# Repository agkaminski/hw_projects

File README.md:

# hw_projects

Various hardware projects that do not deserve their own repository.

## Contents

- [DIYosc](DIYosc) - make your own custom DIP oscilator using HC49 SMD crystal,
- [flipperzero_esp](flipperzero_esp) - expansion module with ESP32 for Flipper Zero,
- [LEDclock](ledclock) - big DIY clock based on LED filaments,
- [picocalc-pi-zero-2](picocalc-pi-zero-2) - Adapter to replace Raspberry Pico with Raspberry Pi Zero in Clockwork PicoCalc.
- [rs232usb](rs232usb) - RS232 to USB-C adapter designed to be pluged directly into the host device,
- [skadis_clock](skadis_clock) - LED clock that fits behind the IKEA SKÅDIS pegboard,
- [usbasp](usbasp) - my realization of the famous [usbasp](https://www.fischl.de/usbasp/),
- [usbasp_mini](usbasp_mini) - miniature version of mine usbasp **design not proven**,
- [VGAtest](VGAtest) - proof of concept 80x40 B&W text mode VGA adapter.

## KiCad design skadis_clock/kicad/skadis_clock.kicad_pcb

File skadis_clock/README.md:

# skadis-clock

LED digital clock that fits behind the IKEA SKÅDIS pegboard.
Uses deformed 7-segment display that shines through pegboard slots.

# PCB

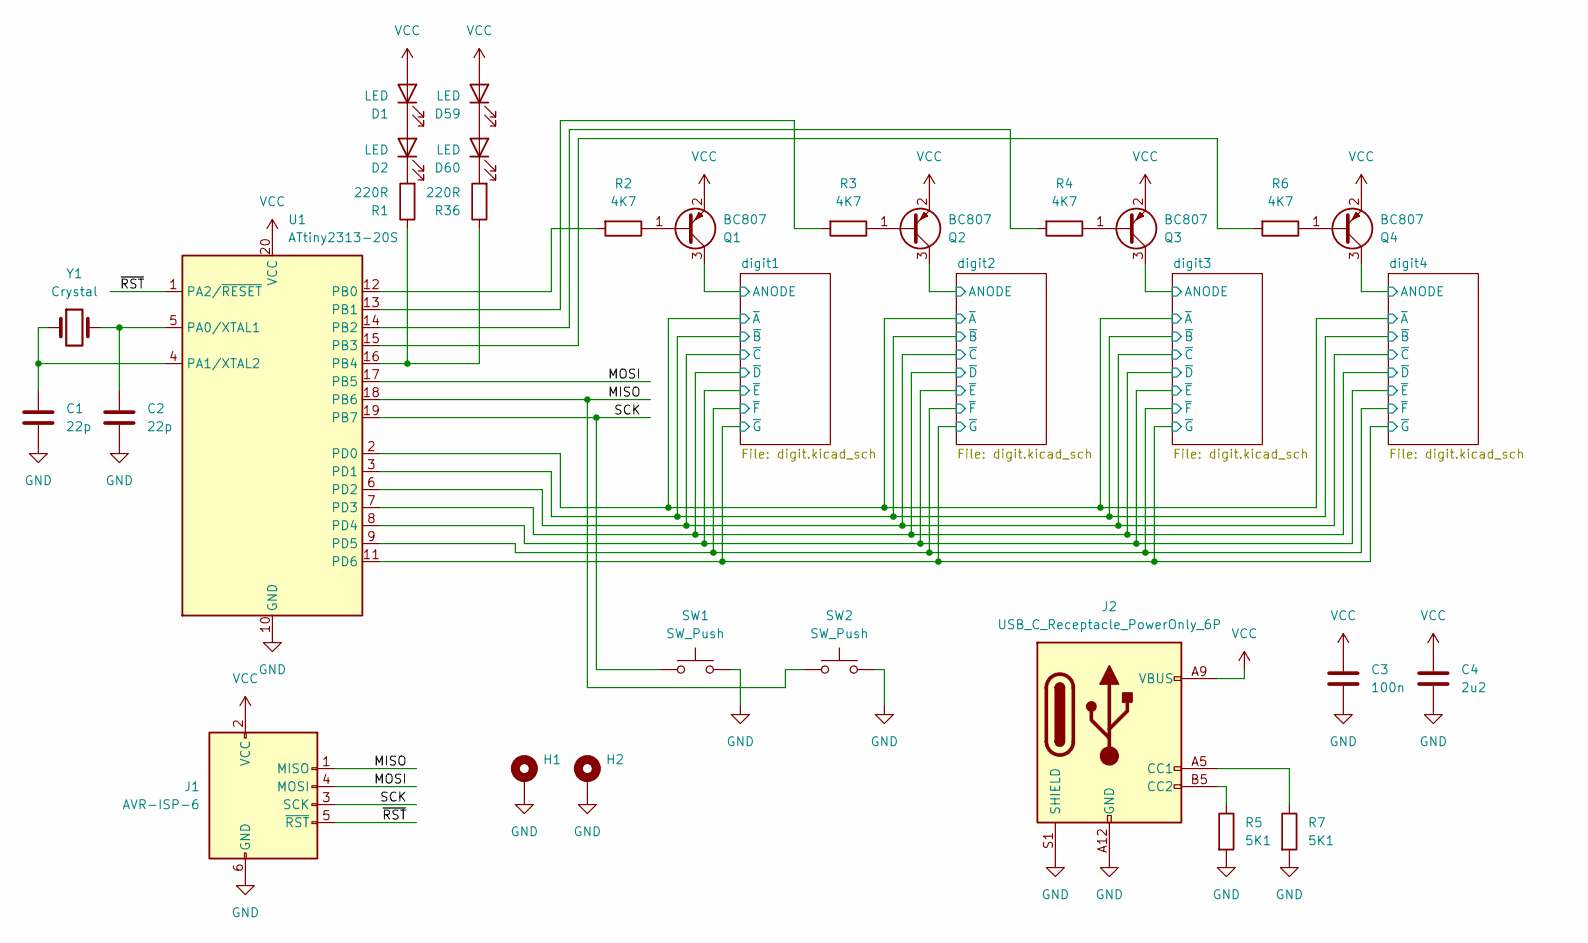
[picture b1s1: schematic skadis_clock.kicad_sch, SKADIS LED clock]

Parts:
C1, C2: 22p; C_0805_2012Metric
C3: 100n; C_0805_2012Metric
C4: 2u2; C_0805_2012Metric
D1, D2, D59, D60: LED; LED_D5.0mm
H1, H2: MountingHole_3.2mm_M3_Pad_Via
J1: AVR-ISP-6; IDC-Header_2x03_P2.54mm_Vertical
J2: USB_C_Receptacle_PowerOnly_6P; USB_C_Receptacle_GCT_USB4125-xx-x-0190_6P_TopMnt_Horizontal
Q1, Q2, Q3, Q4: BC807; SOT-23
R1, R36: 220R; R_0805_2012Metric
R2, R3, R4, R6: 4K7; R_0805_2012Metric
R5, R7: 5K1; R_0805_2012Metric
SW1, SW2: SW_Push; SW_Tactile_SPST_NO_Straight_CK_PTS636Sx25SMTRLFS
U1: ATtiny2313-20S; SOIC-20W_7.5x12.8mm_P1.27mm
Y1: Crystal; Crystal_SMD_HC49-SD

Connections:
/MISO: J1.1 (MISO), SW2.1, U1.18 (PB6)
/MOSI: J1.4 (MOSI), U1.17 (PB5)
/SCK: J1.3 (SCK), SW1.1, U1.19 (PB7)
/digit1/ANODE: Q1.3 (C); also elsewhere on the board
/digit1/~A: U1.2 (PD0); also elsewhere on the board
/digit1/~B: U1.3 (PD1); also elsewhere on the board
/digit1/~C: U1.6 (PD2); also elsewhere on the board
/digit1/~D: U1.7 (PD3); also elsewhere on the board
/digit1/~E: U1.8 (PD4); also elsewhere on the board
/digit1/~F: U1.9 (PD5); also elsewhere on the board
/digit1/~G: U1.11 (PD6); also elsewhere on the board
/digit2/ANODE: Q2.3 (C); also elsewhere on the board
/digit3/ANODE: Q3.3 (C); also elsewhere on the board
/digit4/ANODE: Q4.3 (C); also elsewhere on the board
/~RST: J1.5 (~RST), U1.1 (PA2/~RESET)
GND: C1.2, C2.2, C3.2, C4.2, H1.MP, H2.MP, J1.6 (GND), J2.A12 (GND), J2.B12 (GND), J2.S1 (SHIELD), R5.2, R7.2, SW1.2, SW2.2, U1.10 (GND)
unnamed: D1.1 (K), D2.2 (A)
unnamed: D2.1 (K), R1.2
unnamed: D59.1 (K), D60.2 (A)
unnamed: D60.1 (K), R36.2
unnamed: J2.A5 (CC1), R7.1
unnamed: J2.B5 (CC2), R5.1
unnamed: Q1.1 (B), R2.1
unnamed: Q2.1 (B), R3.1
unnamed: Q3.1 (B), R4.1
unnamed: Q4.1 (B), R6.1
unnamed: C2.1, U1.5 (PA0/XTAL1), Y1.2
unnamed: C1.1, U1.4 (PA1/XTAL2), Y1.1
unnamed: R2.2, U1.12 (PB0)
unnamed: R3.2, U1.13 (PB1)
unnamed: R4.2, U1.14 (PB2)
unnamed: R6.2, U1.15 (PB3)
unnamed: R1.1, R36.1, U1.16 (PB4)
VCC: C3.1, C4.1, D1.2 (A), D59.2 (A), J1.2 (VCC), J2.A9 (VBUS), J2.B9 (VBUS), Q1.2 (E), Q2.2 (E), Q3.2 (E), Q4.2 (E), U1.20 (VCC)

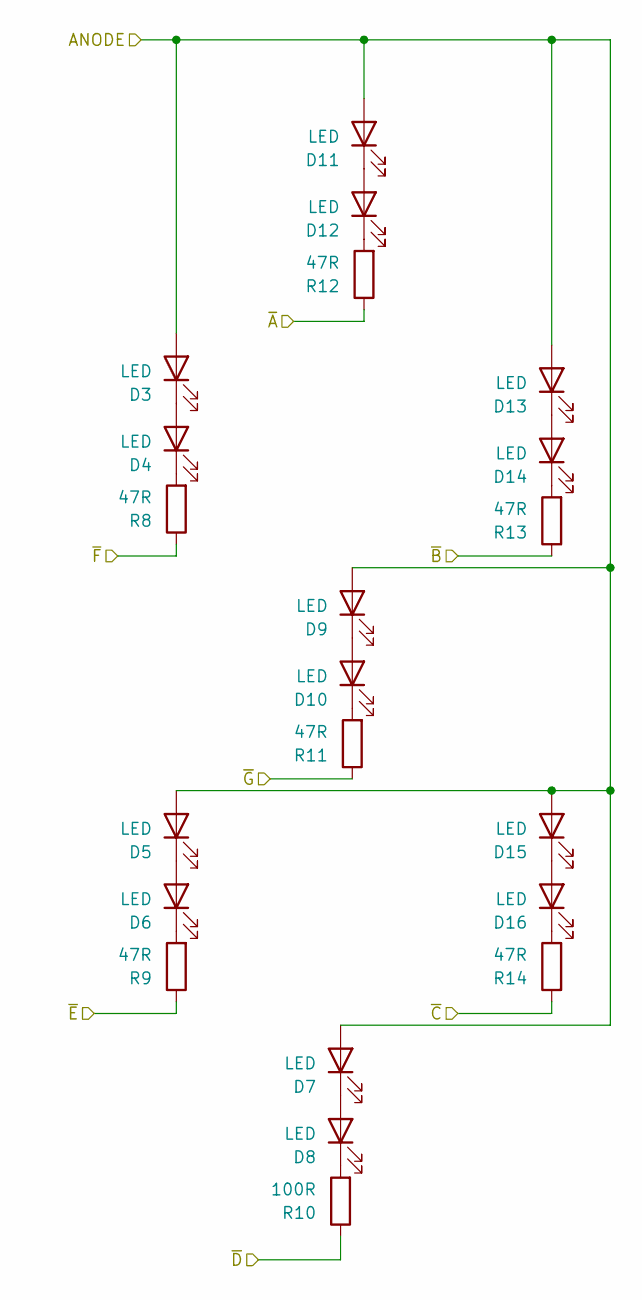
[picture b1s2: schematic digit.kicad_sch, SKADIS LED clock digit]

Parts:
D3, D4, D5, D6, D7, D8, D9, D10, D11, D12, D13, D14, D15, D16: LED; LED_D5.0mm
R8, R9, R11, R12, R13, R14: 47R; R_0805_2012Metric
R10: 100R; R_0805_2012Metric

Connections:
/digit1/ANODE: D3.2 (A), D5.2 (A), D7.2 (A), D9.2 (A), D11.2 (A), D13.2 (A), D15.2 (A); also elsewhere on the board
/digit1/~A: R12.1; also elsewhere on the board
/digit1/~B: R13.1; also elsewhere on the board
/digit1/~C: R14.1; also elsewhere on the board
/digit1/~D: R10.1; also elsewhere on the board
/digit1/~E: R9.1; also elsewhere on the board
/digit1/~F: R8.1; also elsewhere on the board
/digit1/~G: R11.1; also elsewhere on the board
unnamed: D3.1 (K), D4.2 (A)
unnamed: D4.1 (K), R8.2
unnamed: D5.1 (K), D6.2 (A)
unnamed: D6.1 (K), R9.2
unnamed: D7.1 (K), D8.2 (A)
unnamed: D8.1 (K), R10.2
unnamed: D9.1 (K), D10.2 (A)
unnamed: D10.1 (K), R11.2
unnamed: D11.1 (K), D12.2 (A)
unnamed: D12.1 (K), R12.2
unnamed: D13.1 (K), D14.2 (A)
unnamed: D14.1 (K), R13.2
unnamed: D15.1 (K), D16.2 (A)
unnamed: D16.1 (K), R14.2

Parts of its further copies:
D17, D18, D19, D20, D21, D22, D23, D24, D25, D26, D27, D28, D29, D30, D31, D32, D33, D34, D35, D36, D37, D38, D39, D40, D41, D42, D43, D44, D45, D46, D47, D48, D49, D50, D51, D52, D53, D54, D55, D56, D57, D58: LED; LED_D5.0mm
R15, R16, R18, R19, R20, R21, R22, R23, R25, R26, R27, R28, R29, R30, R32, R33, R34, R35: 47R; R_0805_2012Metric
R17, R24, R31: 100R; R_0805_2012Metric

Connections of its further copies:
/digit1/~A: R19.1, R26.1, R33.1; also elsewhere on the board
/digit1/~B: R20.1, R27.1, R34.1; also elsewhere on the board
/digit1/~C: R21.1, R28.1, R35.1; also elsewhere on the board
/digit1/~D: R17.1, R24.1, R31.1; also elsewhere on the board
/digit1/~E: R16.1, R23.1, R30.1; also elsewhere on the board
/digit1/~F: R15.1, R22.1, R29.1; also elsewhere on the board
/digit1/~G: R18.1, R25.1, R32.1; also elsewhere on the board
/digit2/ANODE: D17.2 (A), D19.2 (A), D21.2 (A), D23.2 (A), D25.2 (A), D27.2 (A), D29.2 (A); also elsewhere on the board
/digit3/ANODE: D31.2 (A), D33.2 (A), D35.2 (A), D37.2 (A), D39.2 (A), D41.2 (A), D43.2 (A); also elsewhere on the board
/digit4/ANODE: D45.2 (A), D47.2 (A), D49.2 (A), D51.2 (A), D53.2 (A), D55.2 (A), D57.2 (A); also elsewhere on the board
unnamed: D17.1 (K), D18.2 (A)
unnamed: D18.1 (K), R15.2
unnamed: D19.1 (K), D20.2 (A)
unnamed: D20.1 (K), R16.2
unnamed: D21.1 (K), D22.2 (A)
unnamed: D22.1 (K), R17.2
unnamed: D23.1 (K), D24.2 (A)
unnamed: D24.1 (K), R18.2
unnamed: D25.1 (K), D26.2 (A)
unnamed: D26.1 (K), R19.2
unnamed: D27.1 (K), D28.2 (A)
unnamed: D28.1 (K), R20.2
unnamed: D29.1 (K), D30.2 (A)
unnamed: D30.1 (K), R21.2
unnamed: D31.1 (K), D32.2 (A)
unnamed: D32.1 (K), R22.2
unnamed: D33.1 (K), D34.2 (A)
unnamed: D34.1 (K), R23.2
unnamed: D35.1 (K), D36.2 (A)
unnamed: D36.1 (K), R24.2
unnamed: D37.1 (K), D38.2 (A)
unnamed: D38.1 (K), R25.2
unnamed: D39.1 (K), D40.2 (A)
unnamed: D40.1 (K), R26.2
unnamed: D41.1 (K), D42.2 (A)
unnamed: D42.1 (K), R27.2
unnamed: D43.1 (K), D44.2 (A)
unnamed: D44.1 (K), R28.2
unnamed: D45.1 (K), D46.2 (A)
unnamed: D46.1 (K), R29.2
unnamed: D47.1 (K), D48.2 (A)
unnamed: D48.1 (K), R30.2
unnamed: D49.1 (K), D50.2 (A)
unnamed: D50.1 (K), R31.2
unnamed: D51.1 (K), D52.2 (A)
unnamed: D52.1 (K), R32.2
unnamed: D53.1 (K), D54.2 (A)
unnamed: D54.1 (K), R33.2
unnamed: D55.1 (K), D56.2 (A)
unnamed: D56.1 (K), R34.2
unnamed: D57.1 (K), D58.2 (A)
unnamed: D58.1 (K), R35.2

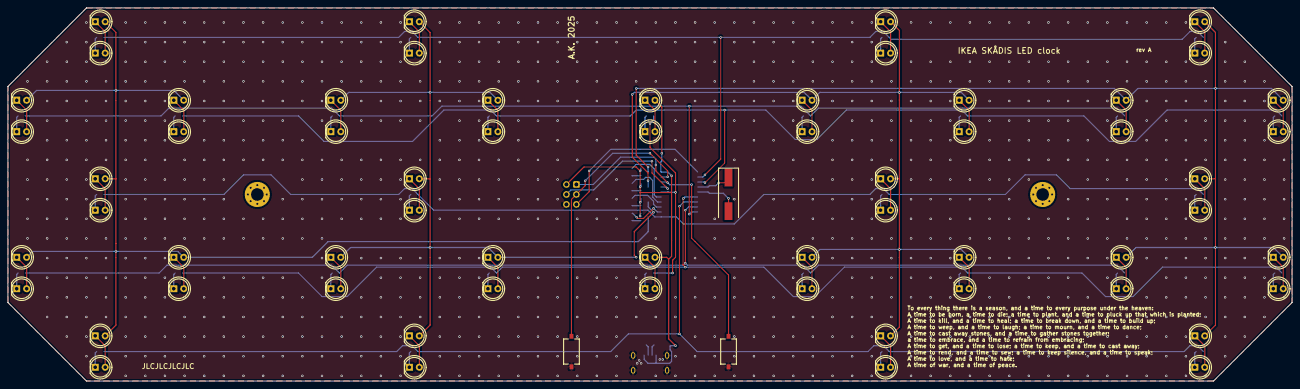
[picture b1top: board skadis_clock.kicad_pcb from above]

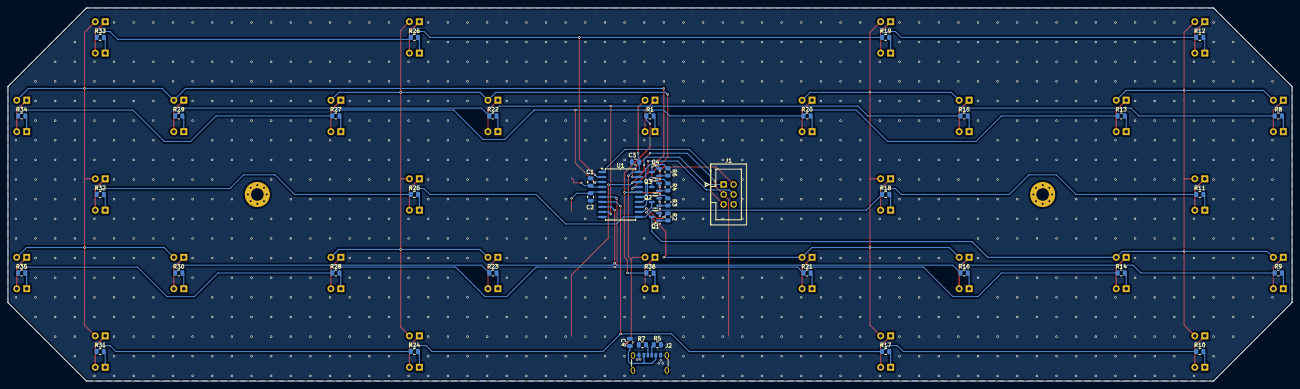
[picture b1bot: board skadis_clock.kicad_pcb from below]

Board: 2 copper layers, 327.0 x 95.0 mm, 112 parts (47 on the bottom side), 90 nets.

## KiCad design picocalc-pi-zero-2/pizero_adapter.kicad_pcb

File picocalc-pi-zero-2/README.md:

# picocalc-pi-zero-2

Adapter to replace Raspberry Pico with Raspberry Pi Zero in Clockwork PicoCalc.

According to [https://github.com/wasdwasd0105/picocalc-pi-zero-2](https://github.com/wasdwasd0105/picocalc-pi-zero-2).

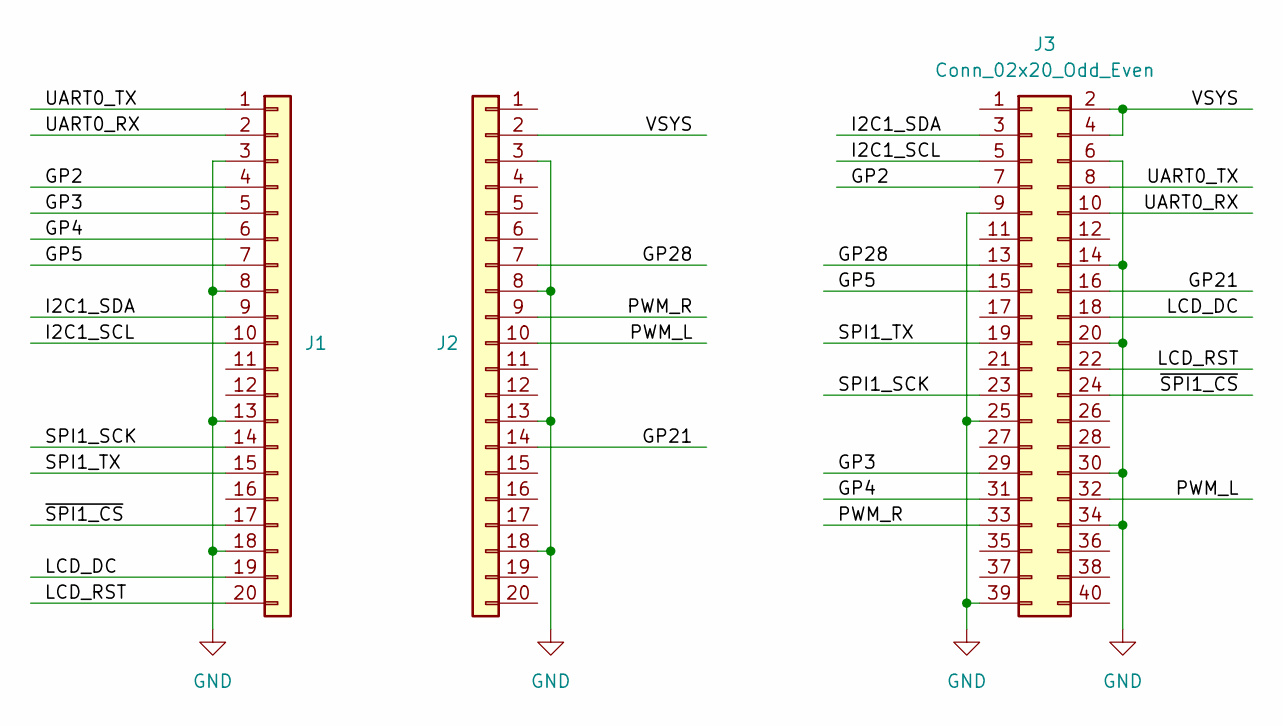
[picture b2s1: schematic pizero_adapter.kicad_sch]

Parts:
J1, J2: Conn_01x20; PinHeader_1x20_P2.54mm_Vertical
J3: Conn_02x20_Odd_Even; PinHeader_2x20_P2.54mm_Vertical

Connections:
/GP2: J1.4, J3.7
/GP3: J1.5, J3.29
/GP4: J1.6, J3.31
/GP5: J1.7, J3.15
/GP21: J2.14, J3.16
/GP28: J2.7, J3.13
/I2C1_SCL: J1.10, J3.5
/I2C1_SDA: J1.9, J3.3
/LCD_DC: J1.19, J3.18
/LCD_RST: J1.20, J3.22
/PWM_L: J2.10, J3.32
/PWM_R: J2.9, J3.33
/SPI1_SCK: J1.14, J3.23
/SPI1_TX: J1.15, J3.19
/UART0_RX: J1.2, J3.10
/UART0_TX: J1.1, J3.8
/VSYS: J2.2, J3.2, J3.4
/~SPI1_CS: J1.17, J3.24
GND: J1.3, J1.8, J1.13, J1.18, J2.3, J2.8, J2.13, J2.18, J3.6, J3.9, J3.14, J3.20, J3.25, J3.30, J3.34, J3.39

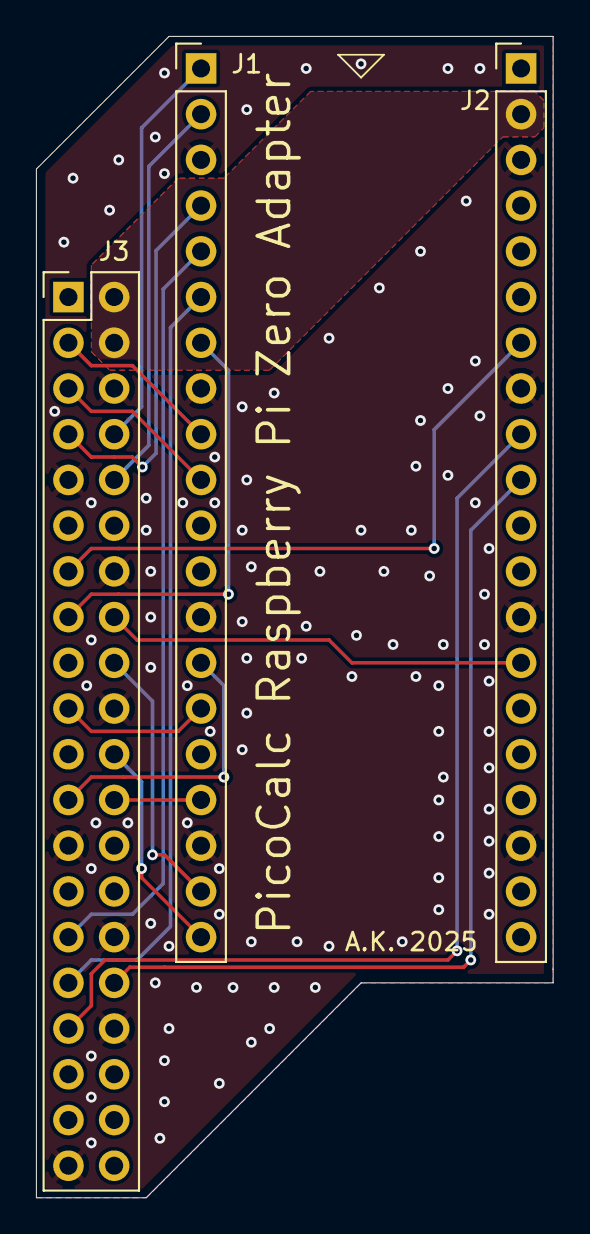
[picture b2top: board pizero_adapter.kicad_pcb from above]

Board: 2 copper layers, 28.7 x 64.5 mm, 3 parts (0 on the bottom side), 19 nets.

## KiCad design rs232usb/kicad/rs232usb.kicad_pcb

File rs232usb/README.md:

# rs232usb

RS232 to USB-C adapter based on CH340N and MAX232.
Designed to be pluged directly into the host device (i.e into male plug).

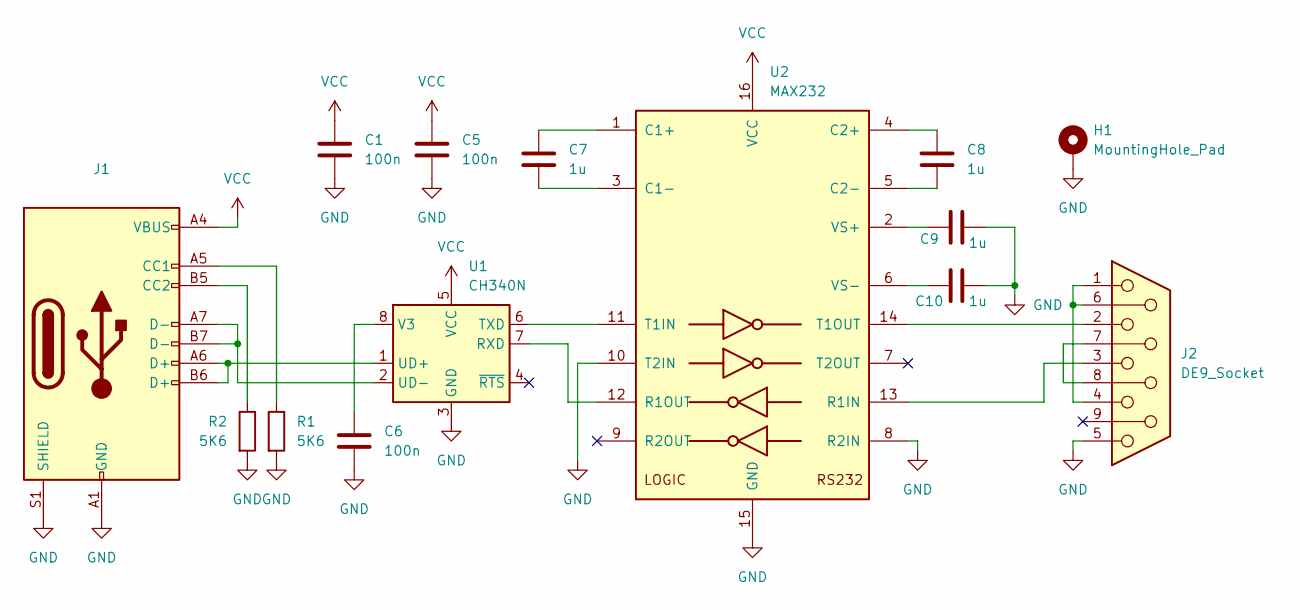
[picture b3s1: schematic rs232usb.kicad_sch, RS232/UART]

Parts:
C1, C5, C6: 100n; C_0805_2012Metric
C7, C8, C9, C10: 1u; C_0805_2012Metric
H1: MountingHole_Pad; MountingHole_3.2mm_M3_Pad_Via
J1: USB_C_Receptacle_USB2.0_14P; USB_C_Receptacle_GCT_USB4105-xx-A_16P_TopMnt_Horizontal
J2: DE9_Socket; DSUB-9_Socket_EdgeMount_P2.77mm
R1, R2: 5K6; R_0805_2012Metric
U1: CH340N; SOP-8_3.9x4.9mm_P1.27mm
U2: MAX232; SOIC-16_3.9x9.9mm_P1.27mm

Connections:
GND: C1.2, C5.2, C6.2, C9.1, C10.1, H1.1, J1.A1 (GND), J1.A12 (GND), J1.B1 (GND), J1.B12 (GND), J1.S1 (SHIELD), J2.5, R1.2, R2.2, U1.3 (GND), U2.8 (R2IN), U2.10 (T2IN), U2.15 (GND)
unnamed: J1.A5 (CC1), R1.1
unnamed: J1.B5 (CC2), R2.1
unnamed: J2.1, J2.4, J2.6
unnamed: J2.7, J2.8
unnamed: U1.7 (RXD), U2.12 (R1OUT)
unnamed: U1.6 (TXD), U2.11 (T1IN)
unnamed: J1.A6 (D+), J1.B6 (D+), U1.1 (UD+)
unnamed: J1.A7 (D-), J1.B7 (D-), U1.2 (UD-)
unnamed: C6.1, U1.8 (V3)
unnamed: C7.1, U2.1 (C1+)
unnamed: C7.2, U2.3 (C1-)
unnamed: C8.2, U2.4 (C2+)
unnamed: C8.1, U2.5 (C2-)
unnamed: J2.3, U2.13 (R1IN)
unnamed: J2.2, U2.14 (T1OUT)
unnamed: C9.2, U2.2 (VS+)
unnamed: C10.2, U2.6 (VS-)
VCC: C1.1, C5.1, J1.A4 (VBUS), J1.A9 (VBUS), J1.B4 (VBUS), J1.B9 (VBUS), U1.5 (VCC), U2.16 (VCC)

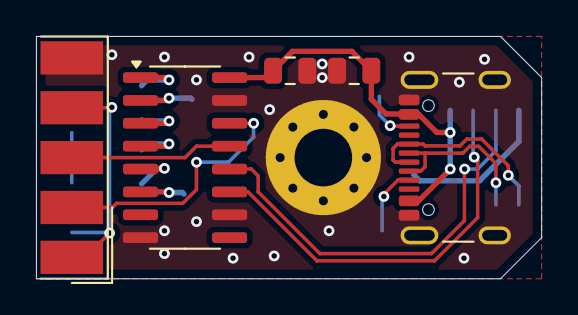
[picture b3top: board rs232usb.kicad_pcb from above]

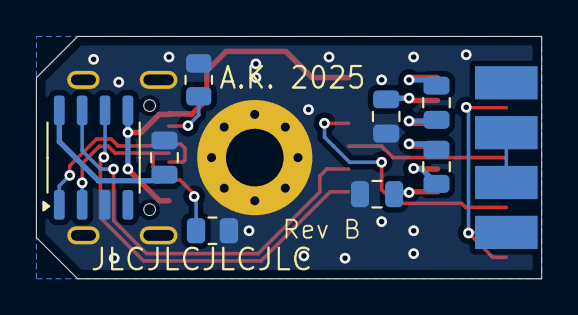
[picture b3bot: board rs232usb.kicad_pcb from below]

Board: 2 copper layers, 28.1 x 13.5 mm, 14 parts (8 on the bottom side), 19 nets.

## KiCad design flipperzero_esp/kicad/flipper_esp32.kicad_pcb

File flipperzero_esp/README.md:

# flipperzero_esp

Expansion module with ESP32 for Flipper Zero.

## Patch

Adapts [ESP flasher app](https://github.com/0xchocolate/flipperzero-esp-flasher) to the changes in pinout I made.

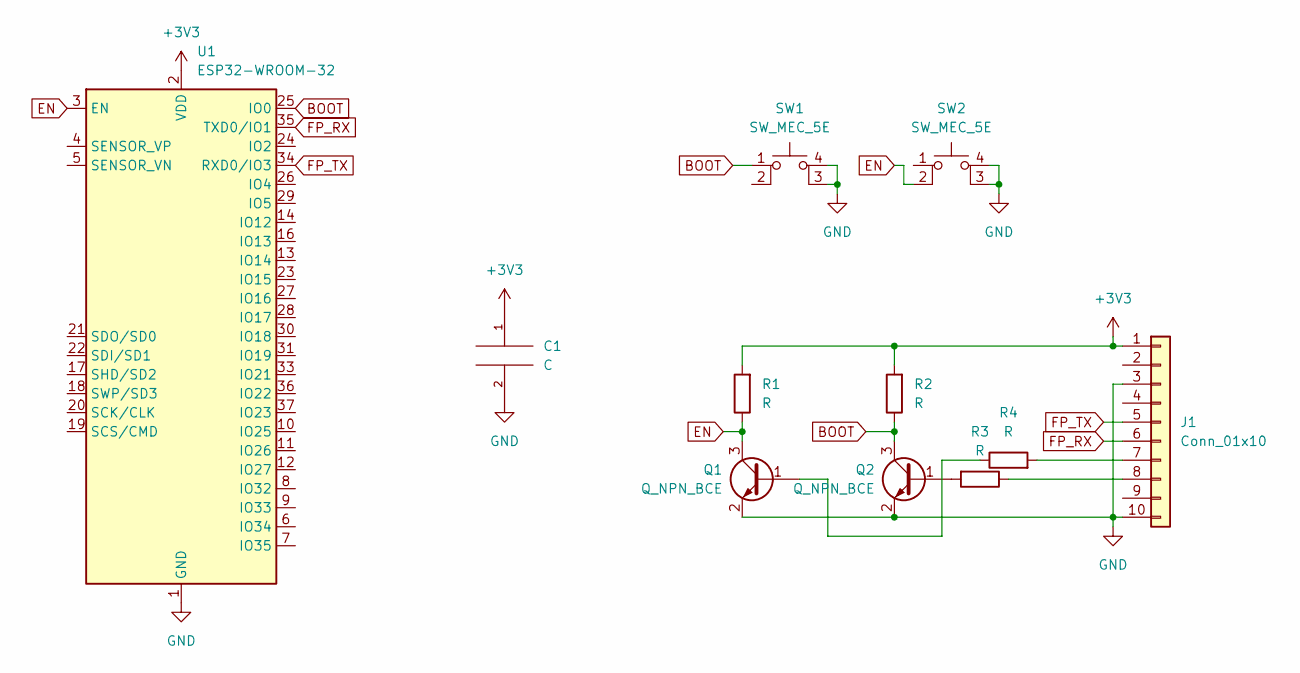
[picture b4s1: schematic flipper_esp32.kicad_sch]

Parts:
C1: C; C_0805_2012Metric_Pad1.18x1.45mm_HandSolder
J1: Conn_01x10; PinSocket_1x10_P2.54mm_Horizontal
Q1, Q2: Q_NPN_BCE; SOT-23W_Handsoldering
R1, R2, R3, R4: R; R_0805_2012Metric_Pad1.20x1.40mm_HandSolder
SW1, SW2: SW_MEC_5E; SW_SPST_Omron_B3FS-101xP
U1: ESP32-WROOM-32

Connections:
+3V3: C1.1, J1.1, R1.2, R2.2, U1.2 (VDD)
BOOT: Q2.3 (E), R2.1, SW1.1, U1.25 (IO0)
EN: Q1.3 (E), R1.1, SW2.2, U1.3 (EN)
FP_RX: J1.6, U1.35 (TXD0/IO1)
FP_TX: J1.5, U1.34 (RXD0/IO3)
GND: C1.2, J1.3, J1.10, Q1.2 (C), Q2.2 (C), SW1.3 (K), SW1.4 (A), SW2.3 (K), SW2.4 (A), U1.1 (GND), U1.15 (GND), U1.38 (GND), U1.39 (GND)
unnamed: J1.7, R4.2
unnamed: J1.8, R3.1
unnamed: Q1.1 (B), R4.1
unnamed: Q2.1 (B), R3.2

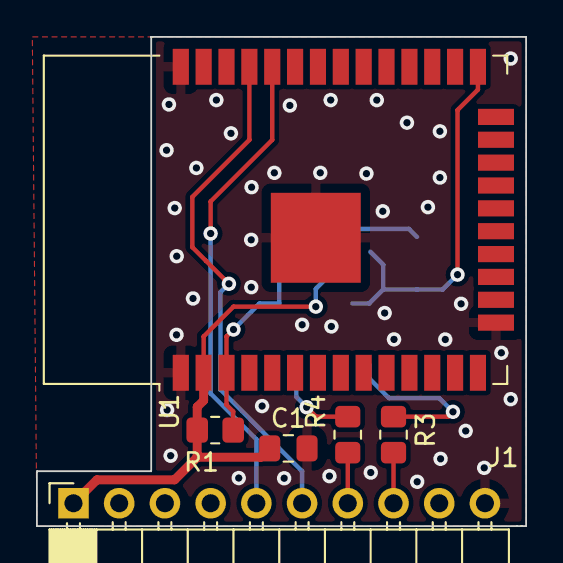
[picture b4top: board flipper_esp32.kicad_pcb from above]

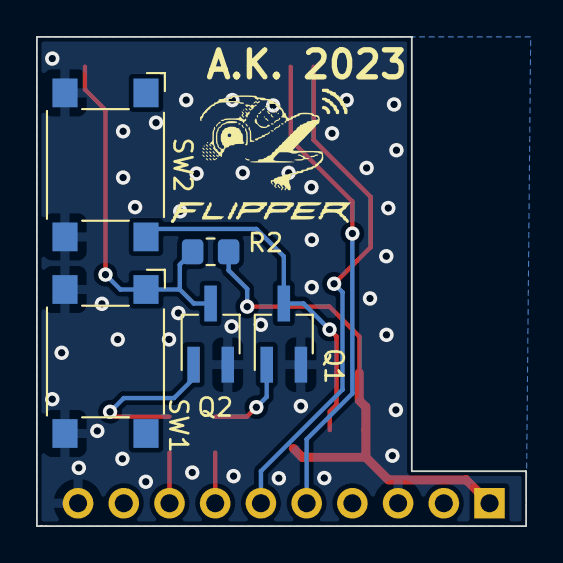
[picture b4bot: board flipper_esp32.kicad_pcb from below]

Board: 2 copper layers, 27.2 x 27.2 mm, 11 parts (5 on the bottom side), 10 nets.

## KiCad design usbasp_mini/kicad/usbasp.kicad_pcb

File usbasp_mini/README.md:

# usbasp_mini

My realization of the famous [usbasp](https://www.fischl.de/usbasp/).
Enhanced with logic level shifters to allow wide range of targed Vdd's.

Miniature version, equiped with the 6 pin ISP connector only.

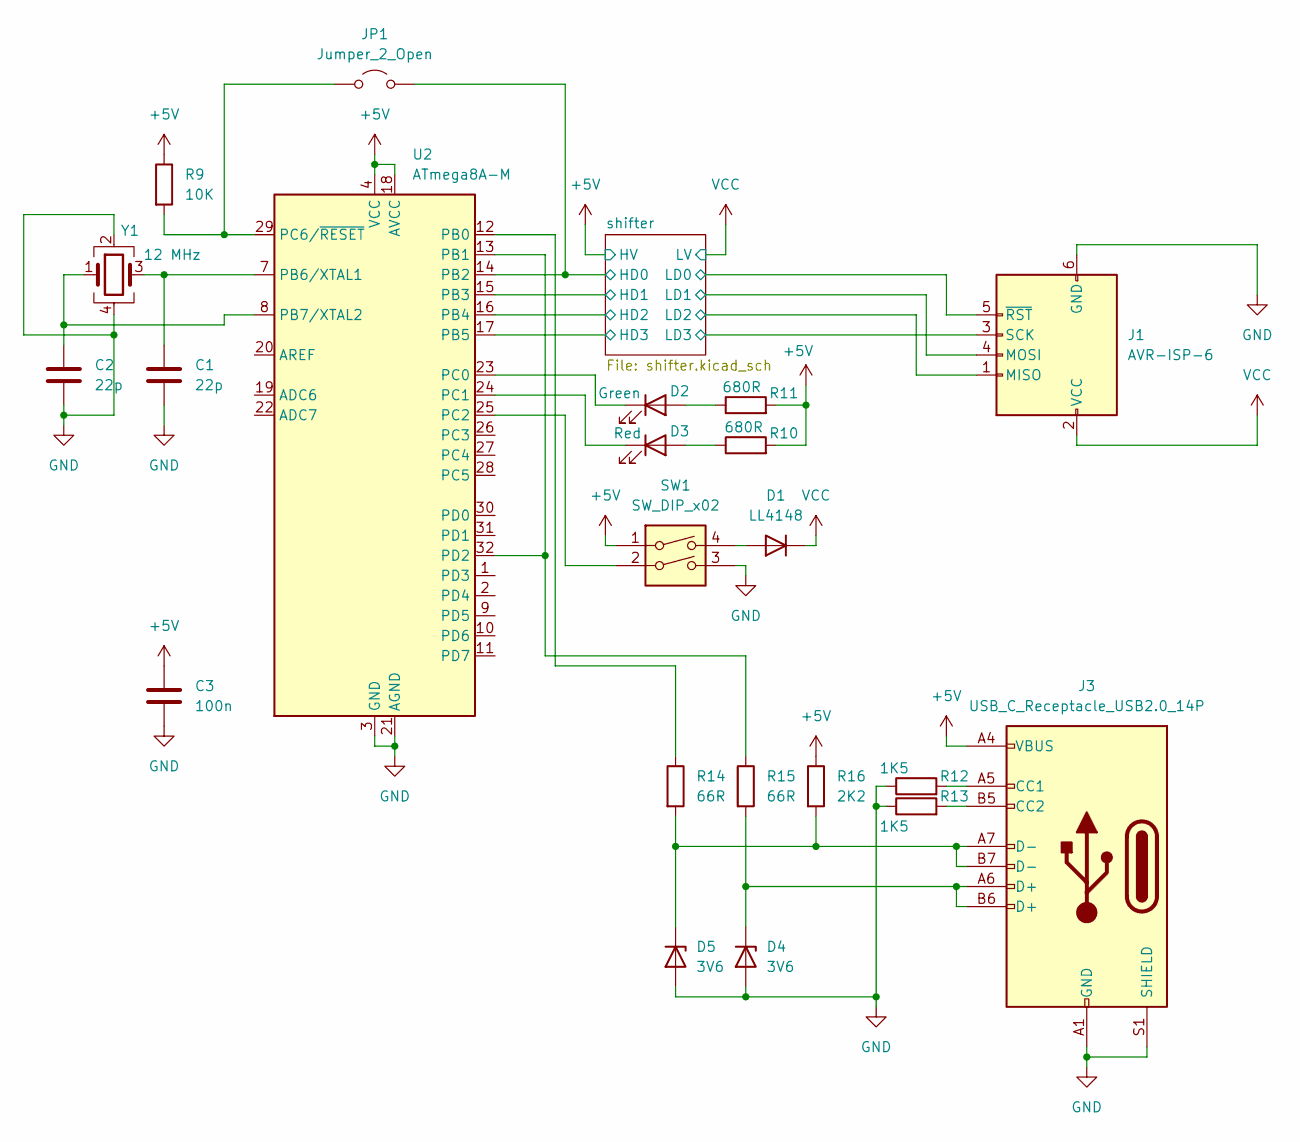
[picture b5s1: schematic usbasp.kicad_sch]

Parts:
C1, C2: 22p; C_0805_2012Metric_Pad1.18x1.45mm_HandSolder
C3: 100n; C_0805_2012Metric_Pad1.18x1.45mm_HandSolder
D1: LL4148; D_MiniMELF
D2: Green; LED_0805_2012Metric_Pad1.15x1.40mm_HandSolder
D3: Red; LED_0805_2012Metric_Pad1.15x1.40mm_HandSolder
D4, D5: 3V6; D_MiniMELF
J1: AVR-ISP-6; Edge6
J3: USB_C_Receptacle_USB2.0_14P; USB_C_Receptacle_GCT_USB4105-xx-A_16P_TopMnt_Horizontal
JP1: Jumper_2_Open; SolderJumper-2_P1.3mm_Open_TrianglePad1.0x1.5mm
R9: 10K; R_0805_2012Metric_Pad1.20x1.40mm_HandSolder
R10, R11: 680R; R_0805_2012Metric_Pad1.20x1.40mm_HandSolder
R12, R13: 1K5; R_0805_2012Metric_Pad1.20x1.40mm_HandSolder
R14, R15: 66R; R_0805_2012Metric_Pad1.20x1.40mm_HandSolder
R16: 2K2; R_0805_2012Metric_Pad1.20x1.40mm_HandSolder
SW1: SW_DIP_x02; SW_DIP_SPSTx02_Slide_9.78x7.26mm_W7.62mm_P2.54mm
U2: ATmega8A-M; QFN-32-1EP_5x5mm_P0.5mm_EP3.1x3.1mm
Y1: 12 MHz; Crystal_SMD_Abracon_ABM3C-4Pin_5.0x3.2mm

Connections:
+5V: C3.1, J3.A4 (VBUS), J3.A9 (VBUS), J3.B4 (VBUS), J3.B9 (VBUS), R9.1, R10.2, R11.2, R16.1, SW1.1, U2.4 (VCC), U2.6 (VCC), U2.18 (AVCC); also elsewhere on the board
/shifter/HD0: JP1.2 (B), U2.14 (PB2); also elsewhere on the board
/shifter/HD1: U2.15 (PB3); also elsewhere on the board
/shifter/HD2: U2.16 (PB4); also elsewhere on the board
/shifter/HD3: U2.17 (PB5); also elsewhere on the board
/shifter/LD0: J1.5 (~RST); also elsewhere on the board
/shifter/LD1: J1.4 (MOSI); also elsewhere on the board
/shifter/LD2: J1.1 (MISO); also elsewhere on the board
/shifter/LD3: J1.3 (SCK); also elsewhere on the board
GND: C1.2, C2.2, C3.2, D4.2 (A), D5.2 (A), J1.6 (GND), J3.A1 (GND), J3.A12 (GND), J3.B1 (GND), J3.B12 (GND), J3.S1 (SHIELD), R12.1, R13.1, SW1.3, U2.3 (GND), U2.5 (GND), U2.21 (AGND), U2.33 (GND), Y1.2, Y1.4
unnamed: D1.2 (A), SW1.4
unnamed: D2.2 (A), R11.1
unnamed: D2.1 (K), U2.23 (PC0)
unnamed: D3.2 (A), R10.1
unnamed: D3.1 (K), U2.24 (PC1)
unnamed: D4.1 (K), J3.A6 (D+), J3.B6 (D+), R15.2
unnamed: D5.1 (K), J3.A7 (D-), J3.B7 (D-), R14.2, R16.2
unnamed: J3.A5 (CC1), R12.2
unnamed: J3.B5 (CC2), R13.2
unnamed: JP1.1 (A), R9.2, U2.29 (PC6/~RESET)
unnamed: R14.1, U2.12 (PB0)
unnamed: R15.1, U2.13 (PB1), U2.32 (PD2)
unnamed: C1.1, U2.7 (PB6/XTAL1), Y1.3
unnamed: C2.1, U2.8 (PB7/XTAL2), Y1.1
unnamed: SW1.2, U2.25 (PC2)
VCC: D1.1 (K), J1.2 (VCC); also elsewhere on the board

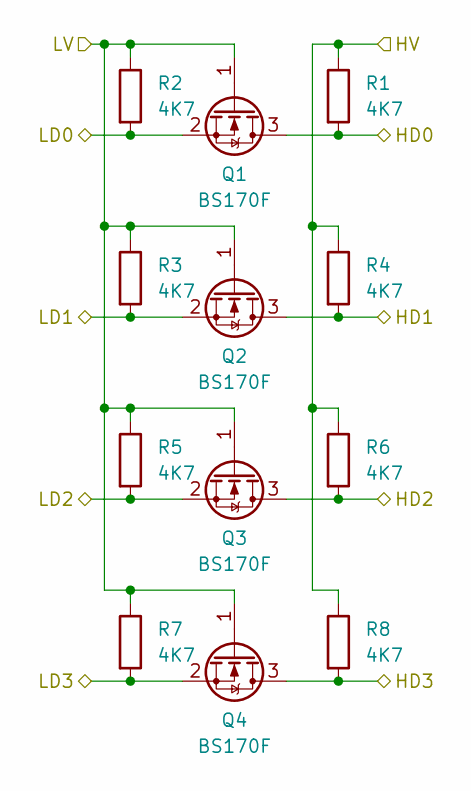
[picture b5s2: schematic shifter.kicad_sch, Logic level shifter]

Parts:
Q1, Q2, Q3, Q4: BS170F; SOT-23
R1, R2, R3, R4, R5, R6, R7, R8: 4K7; R_0805_2012Metric_Pad1.20x1.40mm_HandSolder

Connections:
+5V: R1.1, R4.1, R6.1, R8.1; also elsewhere on the board
/shifter/HD0: Q1.3 (D), R1.2; also elsewhere on the board
/shifter/HD1: Q2.3 (D), R4.2; also elsewhere on the board
/shifter/HD2: Q3.3 (D), R6.2; also elsewhere on the board
/shifter/HD3: Q4.3 (D), R8.2; also elsewhere on the board
/shifter/LD0: Q1.2 (S), R2.2; also elsewhere on the board
/shifter/LD1: Q2.2 (S), R3.2; also elsewhere on the board
/shifter/LD2: Q3.2 (S), R5.2; also elsewhere on the board
/shifter/LD3: Q4.2 (S), R7.2; also elsewhere on the board
VCC: Q1.1 (G), Q2.1 (G), Q3.1 (G), Q4.1 (G), R2.1, R3.1, R5.1, R7.1; also elsewhere on the board

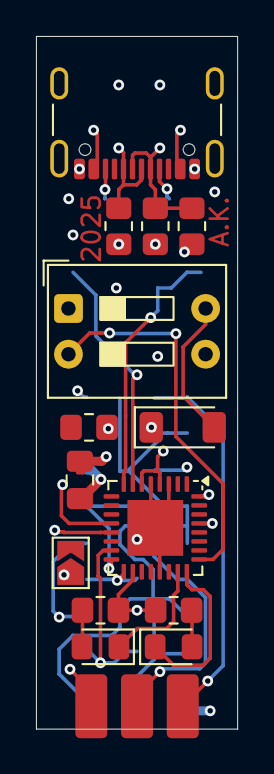
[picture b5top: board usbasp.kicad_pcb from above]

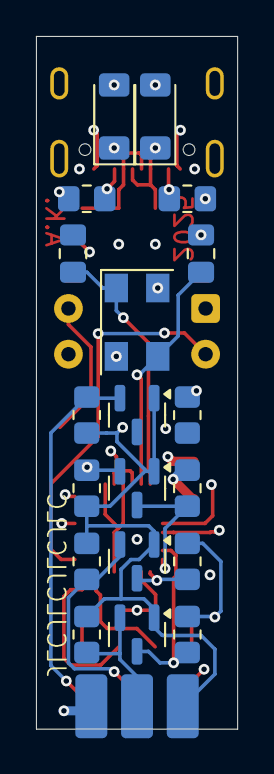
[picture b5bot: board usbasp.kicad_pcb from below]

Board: 4 copper layers, 11.2 x 38.5 mm, 34 parts (19 on the bottom side), 26 nets.

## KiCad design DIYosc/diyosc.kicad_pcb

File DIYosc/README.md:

# DIYosc

I thought I had integrated 8 MHz DIP-14 oscillator, turned out I did not. It
also proved not that easy to buy. But I had 8 MHZ HC49-SD crystals, so I decided
to design a replacement. This PCB should allow usage of pretty much whichever
crystal, but R1, R2, C1 and C2 should be picked accordingly.

# Photos

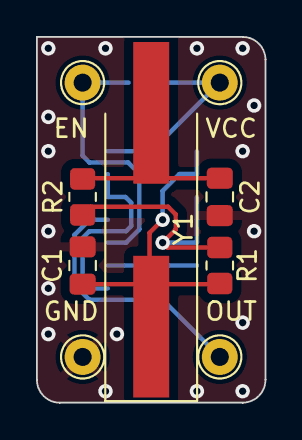
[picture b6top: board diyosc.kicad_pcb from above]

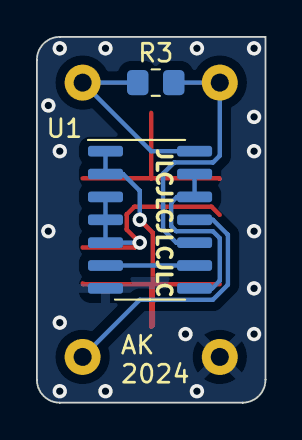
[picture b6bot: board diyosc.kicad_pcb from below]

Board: 2 copper layers, 12.7 x 20.3 mm, 11 parts (2 on the bottom side), 9 nets.

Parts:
C1, C2: 22p; C_0805_2012Metric_Pad1.18x1.45mm_HandSolder
EN: TestPoint_THTPad_D2.0mm_Drill1.0mm
GND: TestPoint_THTPad_D2.0mm_Drill1.0mm
OUT: TestPoint_THTPad_D2.0mm_Drill1.0mm
R1: 1M; R_0805_2012Metric_Pad1.20x1.40mm_HandSolder
R2, R3: 100K; R_0805_2012Metric_Pad1.20x1.40mm_HandSolder
U1: 74HC00; SO-14_3.9x8.65mm_P1.27mm
VCC: TestPoint_THTPad_D2.0mm_Drill1.0mm
Y1: Crystal; Crystal_SMD_HC49-SD_HandSoldering

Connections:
GND: C1.2, C2.2, GND.1, U1.7 (GND)
unnamed: C1.1, R1.1, U1.1, U1.2, Y1.1
unnamed: C2.1, R2.2, Y1.2
unnamed: EN.1, R3.2, U1.10
unnamed: OUT.1, U1.11
unnamed: R1.2, R2.1, U1.3, U1.4, U1.5
unnamed: U1.6, U1.9
unnamed: U1.8, U1.12, U1.13
VCC: R3.1, U1.14 (VCC), VCC.1

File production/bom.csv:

Designator,Footprint,Quantity,Value,LCSC Part #
"C1, C2",0805,2,22p,
"EN, GND, OUT, VCC",TestPoint_THTPad_D2.0mm_Drill1.0mm,4,~,
R1,0805,1,1M,
"R2, R3",0805,2,100K,
U1,SO-14_3.9x8.65mm_P1.27mm,1,74HC00,
Y1,Crystal_SMD_HC49-SD_HandSoldering,1,Crystal,

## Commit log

2025-08-04 Import DIYosc
2025-08-04 Move DIYosc to the separate directory
2025-08-04 Import VGAtest
2025-08-04 Add rs232usb project
2025-08-04 Add usbasp project
2025-08-04 Add usbasp_mini project
2025-08-07 rs232usb: Add case 3D model
2025-08-07 Add Flipper Zero ESP32 module
2025-08-07 Add LEDclock
2025-08-14 Fix rs232usb wrong MAX232 setup
2025-08-27 Add picocalc-pi-zero-2 adapter PCB
2025-09-19 picocalc-pi-zero-2: move rpi to clear the case
2025-10-11 Add skadis-clock
2025-10-11 skadis_clock: Add initial FW (based on ledclock)
2025-10-25 skadis_clock: Set external xtal @8MHz
2025-10-25 skadis_clock: Adapt 7seg decoder
2025-10-25 skadis_clock: fix pin config
2025-10-25 skadis_clock: increase pwm frequency
2025-10-25 skadis_clock: fix RTC timer config
2025-10-25 skadis_clock: change RTC frequency to 1KHz
2025-10-25 README: Fix broken link
2025-10-25 skadis_clock: update binary
2025-10-25 skadis_clock: add 3d models (mount and diffuser)
2025-10-26 skadis_clock: increase pwm prescaler /8 -> /64
2025-10-26 skadis_clock: fix RTC timer off-by-one error
